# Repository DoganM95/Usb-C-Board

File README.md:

# Usb-C-Pcb

This repository contains the design files for a simple yet versatile USB-C PCB. It's designed to deliver 5 volts with USB 2.0 data pin support and includes power delivery capabilities. And yes, ChatGPT created this readme, so don't wonder.

## PCB Views

<table>
  <tr>
    <td></td>
    <td></td>
  </tr>
</table>

## Features

- **5V Output:** The board outputs a stable 5 volts, suitable for various USB-powered devices.
- **Power Delivery Support:** For power delivery functionality, add two 5.1 KOhm resistors of size 0603 in the designated rectangles.
- **Mounting Holes:** Strategically placed drill holes on the sides allow for easy mounting.
- **Cut Limit Line:** A clearly marked cut limit line indicates the maximum cuttable range of the PCB without losing functionality.
- **Enhanced Power Wires:** Thick VCC and GND wires are designed to support high amperage loads.

## Building Steps

To assemble the USB-C PCB, follow these steps:

1. **Solder the USB-C Port:**
   - Position the USB-C port on the PCB.
   - Solder each pin carefully, ensuring good connection without bridging contacts.

2. **Clean Up Excess Solder:**
   - Inspect the solder joints and use a solder wick to remove any excess solder from the fine pins of the USB-C port.
   - Reheat the solder and apply the wick; the wick will absorb the excess, leaving a clean joint.

3. **Solder the Resistors:**
   - Place the 5.1 KOhm resistors in their designated spots on the PCB.
   - Solder the resistors, ensuring they are securely attached to the board.
  
Feel free to explore the design files, contribute, and suggest improvements to this project.

## Resouces

Helpful docs to get a better understanding of the standard:
- [CC Vconn Signals](https://microchipdeveloper.com/xwiki/bin/view/applications/usb/typec-features/cc-vconn-signals/)

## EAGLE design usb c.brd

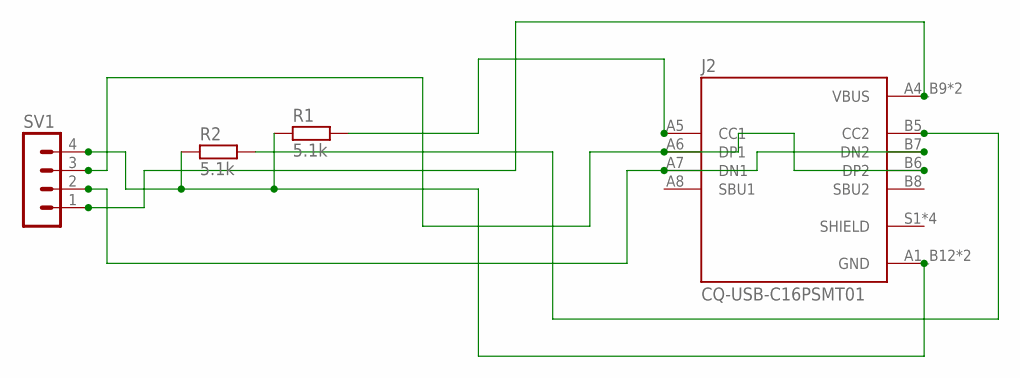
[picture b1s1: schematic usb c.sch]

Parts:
J2: CQ-USB-C16PSMT01; SHENZHEN-CHUANGQIN-TECHNOLOGY_CQ-USB-C16PSMT01
R1, R2: 5.1k; R0603
SV1: MA04-1

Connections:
CC1: J2.A5 (CC1), R1.2
CC2: J2.B5 (CC2), R2.2
DN1: J2.A7 (DN1), J2.B7 (DN2), SV1.2
DP1: J2.A6 (DP1), J2.B6 (DP2), SV1.3
GND: J2.A1_B12 (GND), J2.B1_A12 (GND), R1.1, R2.1, SV1.4
VBUS: J2.A4_B9 (VBUS), J2.B4_A9 (VBUS), SV1.1

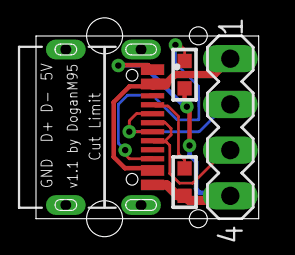
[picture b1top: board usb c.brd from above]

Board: 2 copper layers, 12.4 x 10.1 mm, 4 parts (0 on the bottom side), 6 nets.

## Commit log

2023-11-09 add building steps
2023-11-09 add eagle schematic files
2023-11-09 change project parent folder
2023-11-10 add assets

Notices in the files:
parts and their libraries:
rc-master-smd: Copyright (C) 2007, Bob Starr
